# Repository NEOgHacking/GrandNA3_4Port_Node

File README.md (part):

# GrandNA3_4Port_Node
GrandNA3_4Port_Node is a DMX network node based on the official grandMA3 onPC 4Port Node 4k. My version also has 4DMX outputs with RDM support, a EtherCON connector for sturdy Ethernet connections and a display with a rotating knob for configuration. It also uses the Neutrik halo connectors with adressable rgb leds to show the status of the connection. But it also has some differences. First it unfortunately doesn't unlock any parameters in the GrandMA onPC software, but its 20x cheaper. About $100 instead of $2000.

# Features
This specific DMX node has some really usefull features.
1. 4DMX outputs with RDM support.
2. Neutrik EtherCON connector for a sturdy and lasting connection. Also support for ARTNET and sACN
3. Color display with a rotary encoder for configuration straigt from the unit itself.
4. UPS (uniteruptable power supply) For when the power cuts out but you still need it or just for battery operation.
5. Wifi card slot for wireless operation with the battery.
6. Powered by a rp2350 for its PIO modules so DMX is correctly implemented and not via a hacked uart or bitbanging a pin.
7. PoE (Power over Ethernet) For easy setup and as little wires as possible.
8. USB-C port for power and data to program the rp2350 or configure it.
9. Cheap PCB. The PCB is 100x72mm 4 layer so its cost is low only $7.

# Motivation
I started on making this DMX network node for a few reasons. First i was using a raspberry pi with a usb DMX dongle, this worked but was hard to set up and only got me 1 DMX universe without RDM. It also wasn't the cheapest setup. I wanted it to be cheaper and have more functionallity. Second I once had the opurtunity to use a grandMA3 onPC 4Port Node 4k at school once and realized how usefull it would be. Then my dumb brain said the same sentence it always says: "I can build that myself for cheaper right?" Next thing you know you are 100 hours deep into the project.

# Design
The design process was a heck of a ride, at first i started with the simple DMX part but then got to the ethernet. I really wanted PoE so started with the ride. It was a heck of a long ride, i think it took up 1/3 of the projects time its really complex. Also the most complex schematic from the whole project. The rest went pretty smooth. I had recently done another big project my 3D Printer mainboard and learned allot from that! So the rest was pretty straight forward, always some small chip changes here and there but apart from that it went well. The case design also went quick didn't have to high of standards for that but still wanted it to look good. After a whole day that was done. 
I used KiCad for PCB design, Onshape for 3D design and VScode for Firmware.

# Use
To use this product first get the firmware uploaded via the arduino IDE or PlatformIO Then just plug it into a ethernet setup and plug in your DMX devices. Thats it! Its that simple! For config use the display with the rotating knob to select universes, ethernet settings, ext.

# Schematic
This is a very long schematic. You can find the whole schematics in .PDF format in the individual PCB design folders. But here are some important ones.
First the main schematic of the main PCB.

Then the schematic of the display module.

And finally the esp wifi module.

# PCB's
So this project has 3 PCB's, first the main PCB that does all the hard work, then a display PCB with a rotary encoder and support components for a bare LCD and finally a custom made WIFI module PCB based on the esp.

(there is a glitch in this game, every project i do i get exactly 3 PCB's)

# Case
For this project there needed to be a case to protect the PCB from the outside world. I did this in onshape and am happy with the end result.

Here is the Onshape link:
https://cad.onshape.com/documents/7a1aa90c6a7c74ef8699231e/w/3ea57ea1703701009a206be9/e/21fe65d6bda3912845cd8de3?renderMode=0&uiState=69a73631645b04a633250657
<details>
  <summary>BOM</summary>
  
# BOM
| Id | Designator | Footprint | Quantity | Designation | Supplier and ref | Column1 | Needed quantity | - | LCSC | MOUSER | Already in another pcb | Enough? | Mrf# | Mfr. | Order Qty. | Unit Price(USD) | Ext.Price(USD) | LCSC#/MOUSER | Package | Min | Mult | SPQ | Availability | Stock Status | Customer Notes | Description | Matched status | Product Link |  |  |  |  |  |  |  |  |  |  |  |  |  |  |  |  |  |  |  |
| --- | --- | --- | --- | --- | --- | --- | --- | --- | --- | --- | --- | --- | --- | --- | --- | --- | --- | --- | --- | --- | --- | --- | --- | --- | --- | --- | --- | --- | --- | --- | --- | --- | --- | --- | --- | --- | --- | --- | --- | --- | --- | --- | --- | --- | --- | --- | --- |
| 17 | BT1 | JST_XH_B3B-XH-A_1x03_P2.50mm_Vertical | 1 | Battery_Cell |  |  | 2 |  | x |  |  |  | B3B-XH-A(LF)(SN) | JST | 10 | $0.05 | $0.50 | C144394 | Through Hole,P=2.5mm | 10 | 10 | 1000 | 61980 | In Stock |  | Connector Header 3 position 2.5mm Pitch 3A Through Hole -25?~+85? | Exact Matches | https://www.lcsc.com/product-detail/C144394.html |  |  |  |  |  |  |  |  |  |  |  |  |  |  |  |  |  |  |  |
| 6 | C12,C7,C5,C13,C11,C4,C6,C3,C9,C10,C8,C1 | C_0402_1005Metric | 12 | 100n |  |  | 24 |  | x |  |  |  | CL05B104KO5NNNC | Samsung Electro-Mechanics | 100 | $0.00 | $0.13 | C1525 | 402 | 100 | 100 | 10000 | 22016000 | In Stock |  | 100nF �10% 16V Ceramic Capacitor X7R 0402 | Exact Matches | https://www.lcsc.com/product-detail/C1525.html |  |  |  |  |  |  |  |  |  |  |  |  |  |  |  |  |  |  |  |
| 37 | C17,C19 | C_0402_1005Metric | 2 | 15p |  |  | 4 |  | x |  |  |  | CL05C150JB5NNNC | Samsung Electro-Mechanics | 100 | $0.00 | $0.37 | C86285 | 402 | 100 | 100 | 10000 | 454800 | In Stock |  | 15pF �5% 50V Ceramic Capacitor C0G 0402 | Exact Matches | https://www.lcsc.com/product-detail/C86285.html |  |  |  |  |  |  |  |  |  |  |  |  |  |  |  |  |  |  |  |
| 3 | C2,C15,C16,C14 | C_0402_1005Metric | 4 | 4u7 |  |  | 8 |  | x |  |  |  | CL05A475KP5NRNC | Samsung Electro-Mechanics | 50 | $0.01 | $0.31 | C368809 | 402 | 50 | 50 | 10000 | 5001000 | In Stock |  | 4.7uF �10% 10V Ceramic Capacitor X5R 0402 | Exact Matches | https://www.lcsc.com/product-detail/C368809.html |  |  |  |  |  |  |  |  |  |  |  |  |  |  |  |  |  |  |  |
| 9 | C20,C23,C57,C33,C21 | C_0603_1608Metric | 5 | 10n |  |  | 10 |  | x |  |  |  | CL10B103KC8NNNC | Samsung Electro-Mechanics | 100 | $0.01 | $0.62 | C84709 | 603 | 100 | 100 | 4000 | 18800 | In Stock |  | 10nF �10% 100V Ceramic Capacitor X7R 0603 | Exact Matches | https://www.lcsc.com/product-detail/C84709.html |  |  |  |  |  |  |  |  |  |  |  |  |  |  |  |  |  |  |  |
| 15 | C22,C36,C39,C41,C34,C38,C63,C37,C65,C47,C40,C35 | C_0603_1608Metric | 12 | 1n |  |  | 24 |  | x |  |  |  | CL10B102KC8NNNC | Samsung Electro-Mechanics | 50 | $0.01 | $0.25 | C153291 | 603 | 50 | 50 | 4000 | 107650 | In Stock |  | 1nF �10% 100V Ceramic Capacitor X7R 0603 | Exact Matches | https://www.lcsc.com/product-detail/C153291.html |  |  |  |  |  |  |  |  |  |  |  |  |  |  |  |  |  |  |  |
| 5 | C27,C76,C72,C70,C73,C64,C79,C60,C28,C74,C29,C88,C43,C78,C61,C71,C30,C66,C69,C68,C25,C42,C75,C67,C45,C31,C18,C26,C77 | C_0603_1608Metric | 29 | 100n |  |  | 58 |  | x |  |  |  | CL10B104KC8NNNC | Samsung Electro-Mechanics | 100 | $0.01 | $0.65 | C15725 | 603 | 50 | 50 | 4000 | 175750 | In Stock |  | 100nF �10% 100V Ceramic Capacitor X7R 0603 | Exact Matches | https://www.lcsc.com/product-detail/C15725.html |  |  |  |  |  |  |  |  |  |  |  |  |  |  |  |  |  |  |  |
| 63 | C32,C24 | CP_EIA-2012-12_Kemet-R | 2 | 10u |  |  | 4 |  | x |  |  |  | T491A106K006AT | KEMET | 5 | $0.18 | $0.91 | C122260 | CASE-A-3216-18(mm) | 5 | 5 | 2000 | 1980 | In Stock |  | 10uF �10% 6.3V Tantalum Capacitors 4?@100kHz CASE-A-3216-18(mm) | Exact Matches | https://www.lcsc.com/product-detail/C122260.html |  |  |  |  |  |  |  |  |  |  |  |  |  |  |  |  |  |  |  |
| 50 | C46,C44 | C_0603_1608Metric | 2 | 6.8n |  |  | 4 |  | x |  |  |  | CL10B682KB8NNNC | Samsung Electro-Mechanics | 100 | $0.01 | $0.68 | C84723 | 603 | 100 | 100 | 4000 | 5300 | In Stock |  | 6.8nF �10% 50V Ceramic Capacitor X7R 0603 | Exact Matches | https://www.lcsc.com/product-detail/C84723.html |  |  |  |  |  |  |  |  |  |  |  |  |  |  |  |  |  |  |  |
| 8 | C48,C49 | C_0603_1608Metric | 2 | 10p |  |  | 4 |  | x |  |  |  | CL10C100JB8NNNC | Samsung Electro-Mechanics | 100 | $0.01 | $0.50 | C1634 | 603 | 100 | 100 | 4000 | 1498600 | In Stock |  | 10pF �5% 50V Ceramic Capacitor C0G 0603 | Exact Matches | https://www.lcsc.com/product-detail/C1634.html |  |  |  |  |  |  |  |  |  |  |  |  |  |  |  |  |  |  |  |
| 41 | C52,C51,C50 | C_0805_2012Metric | 3 | 1u |  |  | 6 |  | x |  |  |  | C2012X7S2A105KT000N | TDK | 10 | $0.11 | $1.12 | C342785 | 805 | 5 | 5 | 2000 | 5645 | In Stock |  | 1uF �10% 100V Ceramic Capacitor X7S 0805 | Exact Matches | https://www.lcsc.com/product-detail/C342785.html |  |  |  |  |  |  |  |  |  |  |  |  |  |  |  |  |  |  |  |
| 57 | C53 | CP_Elec_6.3x5.8 | 1 | 10u |  |  | 2 |  | x |  |  |  | EEEFK1J100P | PANASONIC | 5 | $0.14 | $0.71 | C128459 | SMD,D6.3xL5.8mm | 5 | 5 | 1000 | 1420 | In Stock |  | 10uF �20% 63V Aluminum Electrolytic Capacitors 2000hrs@105? | Exact Matches | https://www.lcsc.com/product-detail/C128459.html |  |  |  |  |  |  |  |  |  |  |  |  |  |  |  |  |  |  |  |
| 69 | C54 | C_0603_1608Metric | 1 | 470p |  |  | 2 |  | x |  |  |  | CL10B471KB8NNNC | Samsung Electro-Mechanics | 100 | $0.01 | $0.56 | C22396 | 603 | 100 | 100 | 4000 | 189700 | In Stock |  | 470pF �10% 50V Ceramic Capacitor X7R 0603 | Exact Matches | https://www.lcsc.com/product-detail/C22396.html |  |  |  |  |  |  |  |  |  |  |  |  |  |  |  |  |  |  |  |
| 44 | C55 | CP_Elec_10x10.5 | 1 | 1000u |  |  | 2 |  | x |  |  |  | EEEFT1E102UP | PANASONIC | 2 | $0.78 | $1.55 | C401766 | SMD,D10xL10.2mm | 1 | 1 | 500 | 4041 | In Stock |  | 1000uF �20% 25V Aluminum Electrolytic Capacitors 2000hrs@105? | Exact Matches | https://www.lcsc.com/product-detail/C401766.html |  |  |  |  |  |  |  |  |  |  |  |  |  |  |  |  |  |  |  |
| 52 | C56 | C_1206_3216Metric | 1 | 100u |  |  | 2 |  | x |  |  |  | CL31A107MQHNNNE | Samsung Electro-Mechanics | 10 | $0.06 | $0.61 | C15008 | 1206 | 10 | 10 | 2000 | 6009890 | In Stock |  | 100uF �20% 6.3V Ceramic Capacitor X5R 1206 | Exact Matches | https://www.lcsc.com/product-detail/C15008.html |  |  |  |  |  |  |  |  |  |  |  |  |  |  |  |  |  |  |  |
| 14 | C58 | C_0603_1608Metric | 1 | 4u7 |  |  | 2 |  | x |  |  |  | CL10A475KP8NNNC | Samsung Electro-Mechanics | 50 | $0.01 | $0.28 | C1705 | 603 | 50 | 50 | 4000 | 13333100 | In Stock |  | 4.7uF �10% 10V Ceramic Capacitor X5R 0603 | Exact Matches | https://www.lcsc.com/product-detail/C1705.html |  |  |  |  |  |  |  |  |  |  |  |  |  |  |  |  |  |  |  |
| 20 | C59 | C_0603_1608Metric | 1 | 3.3n |  |  | 2 |  | x |  |  |  | CL10B332KB8NNNC | Samsung Electro-Mechanics | 20 | $0.01 | $0.11 | C1613 | 603 | 20 | 20 | 4000 | 61420 | In Stock |  | 3.3nF �10% 50V Ceramic Capacitor X7R 0603 | Exact Matches | https://www.lcsc.com/product-detail/C1613.html |  |  |  |  |  |  |  |  |  |  |  |  |  |  |  |  |  |  |  |
| 42 | C62 | C_0603_1608Metric | 1 | 15n |  |  | 2 |  | x |  |  |  | CL10B153KB8NNNC | Samsung Electro-Mechanics | 20 | $0.01 | $0.16 | C296713 | 603 | 20 | 20 | 4000 | 39800 | In Stock |  | 15nF �10% 50V Ceramic Capacitor X7R 0603 | Exact Matches | https://www.lcsc.com/product-detail/C296713.html |  |  |  |  |  |  |  |  |  |  |  |  |  |  |  |  |  |  |  |
| 10 | C80,C81 | C_0603_1608Metric | 2 | 1u |  |  | 4 |  | x |  |  |  | CL10A105KB8NNNC | Samsung Electro-Mechanics | 50 | $0.01 | $0.28 | C15849 | 603 | 50 | 50 | 4000 | 4548950 | In Stock |  | 1uF �10% 50V Ceramic Capacitor X5R 0603 | Exact Matches | https://www.lcsc.com/product-detail/C15849.html |  |  |  |  |  |  |  |  |  |  |  |  |  |  |  |  |  |  |  |
| 53 | C82,C86,C87,C83,C84 | C_0603_1608Metric | 5 | 10u |  |  | 10 |  | x |  |  |  | CL10A106KP8NNNC | Samsung Electro-Mechanics | 50 | $0.01 | $0.33 | C19702 | 603 | 50 | 50 | 4000 | 13475400 | In Stock |  | 10uF �10% 10V Ceramic Capacitor X5R 0603 | Exact Matches | https://www.lcsc.com/product-detail/C19702.html |  |  |  |  |  |  |  |  |  |  |  |  |  |  |  |  |  |  |  |
| 58 | C85 | C_0603_1608Metric | 1 | 2u2 |  |  | 2 |  | x |  |  |  | CL10A225KO8NNNC | Samsung Electro-Mechanics | 50 | $0.01 | $0.31 | C23630 | 603 | 50 | 50 | 4000 | 5941500 | In Stock |  | 2.2uF �10% 16V Ceramic Capacitor X5R 0603 | Exact Matches | https://www.lcsc.com/product-detail/C23630.html |  |  |  |  |  |  |  |  |  |  |  |  |  |  |  |  |  |  |  |
| 32 | D1 | D_SOD-123F | 1 | DSK24L |  |  | 2 |  | x |  |  |  | DSK24L | LGE | 10 | $0.06 | $0.62 | C19272974 | SOD-123FL | 10 | 10 | 3000 | 2600 | In Stock |  | Diode Independent 40V 2A Surface Mount SOD-123FL | Exact Matches | https://www.lcsc.com/product-detail/C19272974.html |  |  |  |  |  |  |  |  |  |  |  |  |  |  |  |  |  |  |  |
| 56 | D10 | D_SMA | 1 | SS34 |  |  | 2 |  | x |  |  |  | SS34 | GOODWORK | 20 | $0.03 | $0.56 | C908680 | SMA(DO-214AC) | 20 | 20 | 5000 | 202260 | In Stock |  | Diode Independent 40V 3A Surface Mount SMA(DO-214AC) | Exact Matches | https://www.lcsc.com/product-detail/C908680.html |  |  |  |  |  |  |  |  |  |  |  |  |  |  |  |  |  |  |  |
| 49 | D11 | D_SOD-123 | 1 | 1N4148W |  |  | 2 |  | x |  |  |  | 1N4148W-E3-08 | VISHAY | 5 | $0.03 | $0.17 | C241939 | SOD-123 | 5 | 5 | 3000 | 71145 | In Stock |  | Diode Independent 75V 150mA Surface Mount SOD-123 | Exact Matches | https://www.lcsc.com/product-detail/C241939.html |  |  |  |  |  |  |  |  |  |  |  |  |  |  |  |  |  |  |  |
| 66 | D12 | D_SOD-123F | 1 | DFTL30A |  |  | 2 |  | x |  |  |  | P4FL30A_R1_00001 | PANJIT | 5 | $0.09 | $0.43 | C2902532 | SOD-123FL | 5 | 5 | 3000 | 2220 | In Stock |  | 48.4VC Clamp 8.3A@10/1000us Ipp TVS DIODE SOD-123FL | Exact Matches | https://www.lcsc.com/product-detail/C2902532.html |  |  |  |  |  |  |  |  |  |  |  |  |  |  |  |  |  |  |  |
| 11 | D13 | LED-SMD_4P-L1.6-W1.5-TR | 1 | LED_ABGR |  |  | 2 |  | x |  |  |  | DY-S161506BRGC-T5-4T-03 | TONYU | 10 | $0.04 | $0.37 | C7280953 | SMD,1.6x1.5mm | 10 | 10 | 4000 | 1640 | In Stock |  | Red, Green, Blue 630nm LED Indication - Discrete 1.8V~2.4V SMD,1.5x1.6mm | Exact Matches | https://www.lcsc.com/product-detail/C7280953.html |  |  |  |  |  |  |  |  |  |  |  |  |  |  |  |  |  |  |  |
| 28 | D2,D7,D5,D6,D9,D3,D4,D8 | D_SOD-123F | 8 | SL110PL-TP |  |  | 16 |  | x |  |  |  | SL110PL-TP | MCC | 20 | $0.15 | $3.07 | C7080765 | SOD-123FL | 10 | 10 | 2500 | 4140 | In Stock |  | Diode 100V 1A Surface Mount SOD-123FL | Exact Matches | https://www.lcsc.com/product-detail/C7080765.html |  |  |  |  |  |  |  |  |  |  |  |  |  |  |  |  |  |  |  |
| 62 | IC1 | QFN-32-1EP_5x5mm_P0.5mm_EP3.45x3.45mm_ThermalVias | 1 | NPM1300-QEAA-R7 |  |  | 2 |  |  | x |  |  | nPM1300-QEAA-R7 | Nordic Semiconductor | 2 | $1.54 | $3.08 | 949-NPM1300-QEAA-R7 |  |  |  |  |  |  |  |  |  | https://nl.mouser.com/ProductDetail/Nordic-Semiconductor/nPM1300-QEAA-R7?qs=3pZoU%2F6IRTj0hxAp51B2zA%3D%3D |  |  |  |  |  |  |  |  |  |  |  |  |  |  |  |  |  |  |  |
| 33 | J1 | JST_SH_SM03B-SRSS-TB_1x03-1MP_P1.00mm_Horizontal | 1 | Conn_01x03_MountingPin |  |  | 2 |  | x |  |  |  | SM03B-SRSS-TB(LF)(SN) | JST | 5 | $0.17 | $0.87 | C160403 | SMD,P=1mm,Surface Mount,Right Angle | 5 | 5 | 3000 | 47315 | In Stock |  | Connector Header 3 position 1mm Pitch 1A Surface Mount, Right Angle -25?~+85? | Exact Matches | https://www.lcsc.com/product-detail/C160403.html |  |  |  |  |  |  |  |  |  |  |  |  |  |  |  |  |  |  |  |
| 39 | J12 | IDC-Header_2x06_P2.54mm_Vertical | 1 | IDC |  |  | 2 |  | x |  |  |  | 2.54-2*6P | BOOMELE(Boom Precision Elec) | 5 | $0.11 | $0.57 | C9136 | Through Hole,P=2.54mm | 5 | 5 | 220 | 19840 | In Stock |  | Connector IDC Header Through Hole 12 position 2.54mm | Exact Matches | https://www.lcsc.com/product-detail/C9136.html |  |  |  |  |  |  |  |  |  |  |  |  |  |  |  |  |  |  |  |
| 51 | J13 | PinSocket_2x04_P2.54mm_Vertical | 1 | Conn_02x04 |  |  | 2 |  | x |  |  |  | PM254V-12-08-H85 | XFCN | 5 | $0.11 | $0.56 | C2834799 | Through Hole,P=2.54mm | 5 | 5 | 1000 | 26375 | In Stock |  | Female Header 8 Position 2.54mm Pitch Dual Row Through Hole -40?~+105? | Exact Matches | https://www.lcsc.com/product-detail/C2834799.html |  |  |  |  |  |  |  |  |  |  |  |  |  |  |  |  |  |  |  |
| 13 | J2 | USB-C_SMD-TYPE-C-31-M-12_1 | 1 | USB_C_Receptacle_USB2.0_14P |  |  | 2 |  | x |  |  |  | TYPE-C-31-M-12 | Korean Hroparts Elec | 5 | $0.17 | $0.84 | C165948 | SMD | 5 | 5 | 1000 | 263130 | In Stock |  | USB-C (USB TYPE-C) Receptacle Connector 16 Position Surface Mount | Exact Matches | https://www.lcsc.com/product-detail/C165948.html |  |  |  |  |  |  |  |  |  |  |  |  |  |  |  |  |  |  |  |
| 1 | J3 | NE8FAHLRDAE | 1 | RJ45 |  |  | 2 |  |  | x |  |  | NE8FAH-LR-DAE | Neutrik | 2 | $6.73 | $13.46 | 568-NE8FAH-LR-DAE |  |  |  |  |  |  |  |  |  | https://nl.mouser.com/ProductDetail/Neutrik/NE8FAH-LR-DAE?qs=4ASt3YYao0WhX9cY4j%252BFSA%3D%3D |  |  |  |  |  |  |  |  |  |  |  |  |  |  |  |  |  |  |  |
| 12 | J4,J8,J10,J6 | NC5FAH1-LR-DAE | 4 | XLR5 |  |  | 4 |  |  | x |  |  | NC5FAH1-LR-DAE | Neutrik | 4 | $7.79 | $31.16 | 568-NC5FAH1-LR-DAE |  |  |  |  |  |  |  |  |  | https://nl.mouser.com/ProductDetail/Neutrik/NC5FAH1-LR-DAE?qs=6avfeC6zeS5u3oz5Q9UQlw%3D%3D |  |  |  |  |  |  |  |  |  |  |  |  |  |  |  |  |  |  |  |
| 47 | J7,J11,J5,J9 | NC3FAH2-LR-DAE | 4 | XLR3 |  |  | 4 |  |  | x |  |  | NC3FAH2-LR-DAE | Neutrik | 4 | $4.33 | $17.32 | 568-NC3FAH2-LR-DAE |  |  |  |  |  |  |  |  |  | https://nl.mouser.com/ProductDetail/Neutrik/NC3FAH2-LR-DAE?qs=4ASt3YYao0XSl5KoEkZrIA%3D%3D |  |  |  |  |  |  |  |  |  |  |  |  |  |  |  |  |  |  |  |
| 21 | L1 | IND-SMD_L2.0-W1.6_AOTA-B201610S3R3-101-T | 1 | 3.3u |  |  | 2 |  | x |  |  |  | AOTA-B201610S3R3-101-T | ABRACON | 5 | $0.29 | $1.44 | C42411119 | 806 | 5 | 5 | 3000 | 15360 | In Stock |  | 2.1A 3.3uH 115m? 2.4A Molded Inductor 0806 Fixed Inductors RoHS | Exact Matches | https://www.lcsc.com/product-detail/C42411119.html |  |  |  |  |  |  |  |  |  |  |  |  |  |  |  |  |  |  |  |
| 48 | L2 | L_Vishay_IHLP-1616 | 1 | 1u |  |  | 2 |  | x |  |  |  | IHLP1616BZER1R0M11 | VISHAY | 2 | $1.63 | $3.26 | C844978 | 1616 | 1 | 1 | 4000 | 79 | In Stock |  | 4.5A 1uH 27m? 5A �20% 1616 Fixed Inductors RoHS | Exact Matches | https://www.lcsc.com/product-detail/C844978.html |  |  |  |  |  |  |  |  |  |  |  |  |  |  |  |  |  |  |  |
| 22 | L3 | XFMR-SMD_16P-L12.7-W7.1-P1.27-LS9.4-BL | 1 | H2019NLT |  |  | 2 |  | x |  |  |  | H2019NLT | PULSE | 2 | $0.74 | $1.49 | C110250 | SMD,12.7x7.1mm | 1 | 1 | 600 | 2085 | In Stock |  | LAN Transformer 1CT:1CT Surface Mount,12.7x7.1mm | Exact Matches | https://www.lcsc.com/product-detail/C110250.html |  |  |  |  |  |  |  |  |  |  |  |  |  |  |  |  |  |  |  |
| 30 | L4,L5 | L_0805_2012Metric | 2 | 2u2 |  |  | 4 |  | x |  |  |  | MLP2012H2R2MT0S1 | TDK | 10 | $0.08 | $0.84 | C383369 | 805 | 10 | 10 | 4000 | 89820 | In Stock |  | 1A 2.2uH 195m? �20% 0805 Fixed Inductors RoHS | Exact Matches | https://www.lcsc.com/product-detail/C383369.html |  |  |  |  |  |  |  |  |  |  |  |  |  |  |  |  |  |  |  |
| 16 | LED1,LED5,LED6,LED3,LED8,LED10,LED9,LED2,LED4,LED7 | LED-SMD_4P-L1.5-W1.5-BL | 10 | SK6805-EC15 |  |  | 20 |  | x |  |  |  | SK6805-EC15 | OPSCO Optoelectronics | 45 | $0.09 | $4.04 | C2890035 | SMD-4P,1.5x1.5mm | 5 | 5 | 4500 | 259070 | In Stock |  | SMD-4P,1.5x1.5mm LED Addressable, Specialty RoHS | Exact Matches | https://www.lcsc.com/product-detail/C2890035.html |  |  |  |  |  |  |  |  |  |  |  |  |  |  |  |  |  |  |  |
| 29 | R1,R27,R3 | R_0603_1608Metric | 3 | 1k |  |  | 6 |  | x |  |  |  | RC0603FR-071KL | YAGEO | 100 | $0.00 | $0.14 | C22548 | 603 | 100 | 100 | 5000 | 4596000 | In Stock |  | 100mW 1k? 75V Thick Film Resistor �100ppm/? �1% 0603 Chip Resistor - Surface Mount RoHS | Exact Matches | https://www.lcsc.com/product-detail/C22548.html |  |  |  |  |  |  |  |  |  |  |  |  |  |  |  |  |  |  |  |
| 34 | R11,R43,R7,R42 | R_0603_1608Metric | 4 | 10k |  |  | 8 |  | x |  |  |  | RC0603FR-0710KL | YAGEO | 100 | $0.00 | $0.14 | C98220 | 603 | 100 | 100 | 5000 | 9034300 | In Stock |  | 100mW 10k? 75V Thick Film Resistor �100ppm/? �1% 0603 Chip Resistor - Surface Mount RoHS | Exact Matches | https://www.lcsc.com/product-detail/C98220.html |  |  |  |  |  |  |  |  |  |  |  |  |  |  |  |  |  |  |  |
| 19 | R13,R12,R15,R14 | R_0603_1608Metric | 4 | 33R |  |  | 8 |  | x |  |  |  | RC0603FR-0733RL | YAGEO | 100 | $0.00 | $0.15 | C108661 | 603 | 100 | 100 | 5000 | 1912100 | In Stock |  | 100mW 33? 75V Thick Film Resistor �100ppm/? �1% 0603 Chip Resistor - Surface Mount RoHS | Exact Matches | https://www.lcsc.com/product-detail/C108661.html |  |  |  |  |  |  |  |  |  |  |  |  |  |  |  |  |  |  |  |
| 38 | R16 | R_0603_1608Metric | 1 | 1M |  |  | 2 |  | x |  |  |  | RC0603FR-071ML | YAGEO | 100 | $0.00 | $0.15 | C105578 | 603 | 100 | 100 | 5000 | 711300 | In Stock |  | 100mW 1M? 75V Thick Film Resistor �100ppm/? �1% 0603 Chip Resistor - Surface Mount RoHS | Exact Matches | https://www.lcsc.com/product-detail/C105578.html |  |  |  |  |  |  |  |  |  |  |  |  |  |  |  |  |  |  |  |
| 2 | R18 | R_0603_1608Metric | 1 | 10R |  |  | 2 |  | x |  |  |  | RC0603FR-0710RL | YAGEO | 100 | $0.00 | $0.43 | C109318 | 603 | 100 | 100 | 5000 | 1937200 | In Stock |  | 100mW 10? 75V Thick Film Resistor �1% �200ppm/? 0603 Chip Resistor - Surface Mount RoHS | Exact Matches | https://www.lcsc.com/product-detail/C109318.html |  |  |  |  |  |  |  |  |  |  |  |  |  |  |  |  |  |  |  |
| 72 | R19 | R_0603_1608Metric | 1 | 12.4k |  |  | 2 |  | x |  |  |  | RC0603FR-0712K4L | YAGEO | 100 | $0.00 | $0.15 | C137798 | 603 | 100 | 100 | 5000 | 38200 | In Stock |  | 100mW 12.4k? 75V Thick Film Resistor �100ppm/? �1% 0603 Chip Resistor - Surface Mount RoHS | Exact Matches | https://www.lcsc.com/product-detail/C137798.html |  |  |  |  |  |  |  |  |  |  |  |  |  |  |  |  |  |  |  |
| 54 | R2 | R_0402_1005Metric | 1 | 33R |  |  | 2 |  | x |  |  |  | RC0402FR-0733RL | YAGEO | 100 | $0.00 | $0.08 | C138002 | 402 | 100 | 100 | 10000 | 1384200 | In Stock |  | 62.5mW 33? 50V Thick Film Resistor �100ppm/? �1% 0402 Chip Resistor - Surface Mount RoHS | Exact Matches | https://www.lcsc.com/product-detail/C138002.html |  |  |  |  |  |  |  |  |  |  |  |  |  |  |  |  |  |  |  |
| 73 | R20 | R_0603_1608Metric | 1 | 4.99k |  |  | 2 |  | x |  |  |  | RC0603FR-074K99L | YAGEO | 100 | $0.00 | $0.15 | C114621 | 603 | 100 | 100 | 5000 | 164800 | In Stock |  | 100mW 4.99k? 75V Thick Film Resistor �100ppm/? �1% 0603 Chip Resistor - Surface Mount RoHS | Exact Matches | https://www.lcsc.com/product-detail/C114621.html |  |  |  |  |  |  |  |  |  |  |  |  |  |  |  |  |  |  |  |
| 24 | R21 | R_0603_1608Metric | 1 | 2.05k |  |  | 2 |  | x |  |  |  | RC0603FR-072K05L | YAGEO | 100 | $0.00 | $0.14 | C137751 | 603 | 100 | 100 | 5000 | 7700 | In Stock |  | 100mW 2.05k? 75V Thick Film Resistor �100ppm/? �1% 0603 Chip Resistor - Surface Mount RoHS | Exact Matches | https://www.lcsc.com/product-detail/C137751.html |  |  |  |  |  |  |  |  |  |  |  |  |  |  |  |  |  |  |  |
| 46 | R22,R40,R23,R17,R8 | R_0603_1608Metric | 5 | 0R |  |  | 10 |  | x |  |  |  | RC0603FR-070RL | YAGEO | 100 | $0.00 | $0.13 | C100044 | 603 | 100 | 100 | 5000 | 2174100 | In Stock |  | 0? 100mW 75V Thick Film Resistor �1% 0603 Chip Resistor - Surface Mount RoHS | Exact Matches | https://www.lcsc.com/product-detail/C100044.html |  |  |  |  |  |  |  |  |  |  |  |  |  |  |  |  |  |  |  |
| 55 | R24 | R_0603_1608Metric | 1 | 36.5k |  |  | 2 |  | x |  |  |  | RC0603FR-0736K5L | YAGEO | 100 | $0.00 | $0.14 | C137738 | 603 | 100 | 100 | 5000 | 20500 | In Stock |  | 36.5k? 100mW 75V Thick Film Resistor �100ppm/? �1% 0603 Chip Resistor - Surface Mount RoHS | Exact Matches | https://www.lcsc.com/product-detail/C137738.html |  |  |  |  |  |  |  |  |  |  |  |  |  |  |  |  |  |  |  |
| 68 | R25 | R_0603_1608Metric | 1 | 12.1k |  |  | 2 |  | x |  |  |  | RC0603FR-0712K1L | YAGEO | 100 | $0.00 | $0.18 | C123417 | 603 | 100 | 100 | 5000 | 0 | Backordered |  | 100mW 12.1k? 75V Thick Film Resistor �100ppm/? �1% 0603 Chip Resistor - Surface Mount RoHS | Exact Matches | https://www.lcsc.com/product-detail/C123417.html |  |  |  |  |  |  |  |  |  |  |  |  |  |  |  |  |  |  |  |
| 67 | R26 | R_0603_1608Metric | 1 | 24.9k |  |  | 2 |  | x |  |  |  | RC0603FR-0724K9L | YAGEO | 100 | $0.00 | $0.15 | C137761 | 603 | 100 | 100 | 5000 | 0 | Backordered |  | 100mW 24.9k? 75V Thick Film Resistor �100ppm/? �1% 0603 Chip Resistor - Surface Mount RoHS | Exact Matches | https://www.lcsc.com/product-detail/C137761.html |  |  |  |  |  |  |  |  |  |  |  |  |  |  |  |  |  |  |  |
| 4 | R29,R38,R28,R30,R39,R31,R36,R37 | R_0603_1608Metric | 8 | 348R |  |  | 16 |  | x |  |  |  | RC0603FR-07348RL | YAGEO | 100 | $0.00 | $0.14 | C137742 | 603 | 100 | 100 | 5000 | 6700 | In Stock |  | 100mW 348? 75V Thick Film Resistor �100ppm/? �1% 0603 Chip Resistor - Surface Mount RoHS | Exact Matches | https://www.lcsc.com/product-detail/C137742.html |  |  |  |  |  |  |  |  |  |  |  |  |  |  |  |  |  |  |  |
| 26 | R33,R32,R35,R34 | R_0603_1608Metric | 4 | 133R |  |  | 8 |  | x |  |  |  | RC0603FR-07133RL | YAGEO | 100 | $0.00 | $0.07 | C273752 | 603 | 100 | 100 | 5000 | 0 | Backordered |  | 133? 100mW 75V Thick Film Resistor �100ppm/? �1% 0603 Chip Resistor - Surface Mount RoHS | Exact Matches | https://www.lcsc.com/product-detail/C273752.html |  |  |  |  |  |  |  |  |  |  |  |  |  |  |  |  |  |  |  |
| 61 | R41 | R_0603_1608Metric | 1 | 430k |  |  | 2 |  | x |  |  |  | RC0603FR-07430KL | YAGEO | 100 | $0.00 | $0.15 | C482869 | 603 | 100 | 100 | 5000 | 30900 | In Stock |  | 430k? 100mW 75V Thick Film Resistor �100ppm/? �1% 0603 Chip Resistor - Surface Mount RoHS | Exact Matches | https://www.lcsc.com/product-detail/C482869.html |  |  |  |  |  |  |  |  |  |  |  |  |  |  |  |  |  |  |  |
| 7 | R5,R4 | R_0402_1005Metric | 2 | 27R |  |  | 4 |  | x |  |  |  | RC0402FR-0727RL | YAGEO | 100 | $0.00 | $0.09 | C138021 | 402 | 100 | 100 | 10000 | 134000 | In Stock |  | 27? �1% 62.5mW 0402 Thick Film Resistor | Exact Matches | https://www.lcsc.com/product-detail/C138021.html |  |  |  |  |  |  |  |  |  |  |  |  |  |  |  |  |  |  |  |
| 64 | R6 | R_0402_1005Metric | 1 | 1k |  |  | 2 |  | x |  |  |  | RC0402FR-071KL | YAGEO | 100 | $0.00 | $0.08 | C106235 | 402 | 100 | 100 | 10000 | 5619500 | In Stock |  | 1k? 62.5mW 50V Thick Film Resistor �100ppm/? �1% 0402 Chip Resistor - Surface Mount RoHS | Exact Matches | https://www.lcsc.com/product-detail/C106235.html |  |  |  |  |  |  |  |  |  |  |  |  |  |  |  |  |  |  |  |
| 45 | REF**,REF**,REF** | NLR-LB | 3 | NLR-LB |  |  | 6 |  |  | x |  |  | NLR-LB | Neutrik | 6 | $1.01 | $6.06 | 568-NLR-LB |  |  |  |  |  |  |  |  |  | https://nl.mouser.com/ProductDetail/Neutrik/NLR-LB?qs=Imq1NPwxi76abBKVKeKReg%3D%3D |  |  |  |  |  |  |  |  |  |  |  |  |  |  |  |  |  |  |  |
| 36 | RN1,RN2 | R_Array_Concave_4x0603 | 2 | 75R |  |  | 4 |  | x |  |  |  | RTA03-4D750JTP | RALEC | 100 | $0.01 | $0.50 | C102680 | 0603x4 | 100 | 100 | 5000 | 584400 | In Stock |  | 4 �5% 75? 62.5mW �200ppm/? 0603x4 Resistor Networks, Arrays RoHS | Exact Matches | https://www.lcsc.com/product-detail/C102680.html |  |  |  |  |  |  |  |  |  |  |  |  |  |  |  |  |  |  |  |
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
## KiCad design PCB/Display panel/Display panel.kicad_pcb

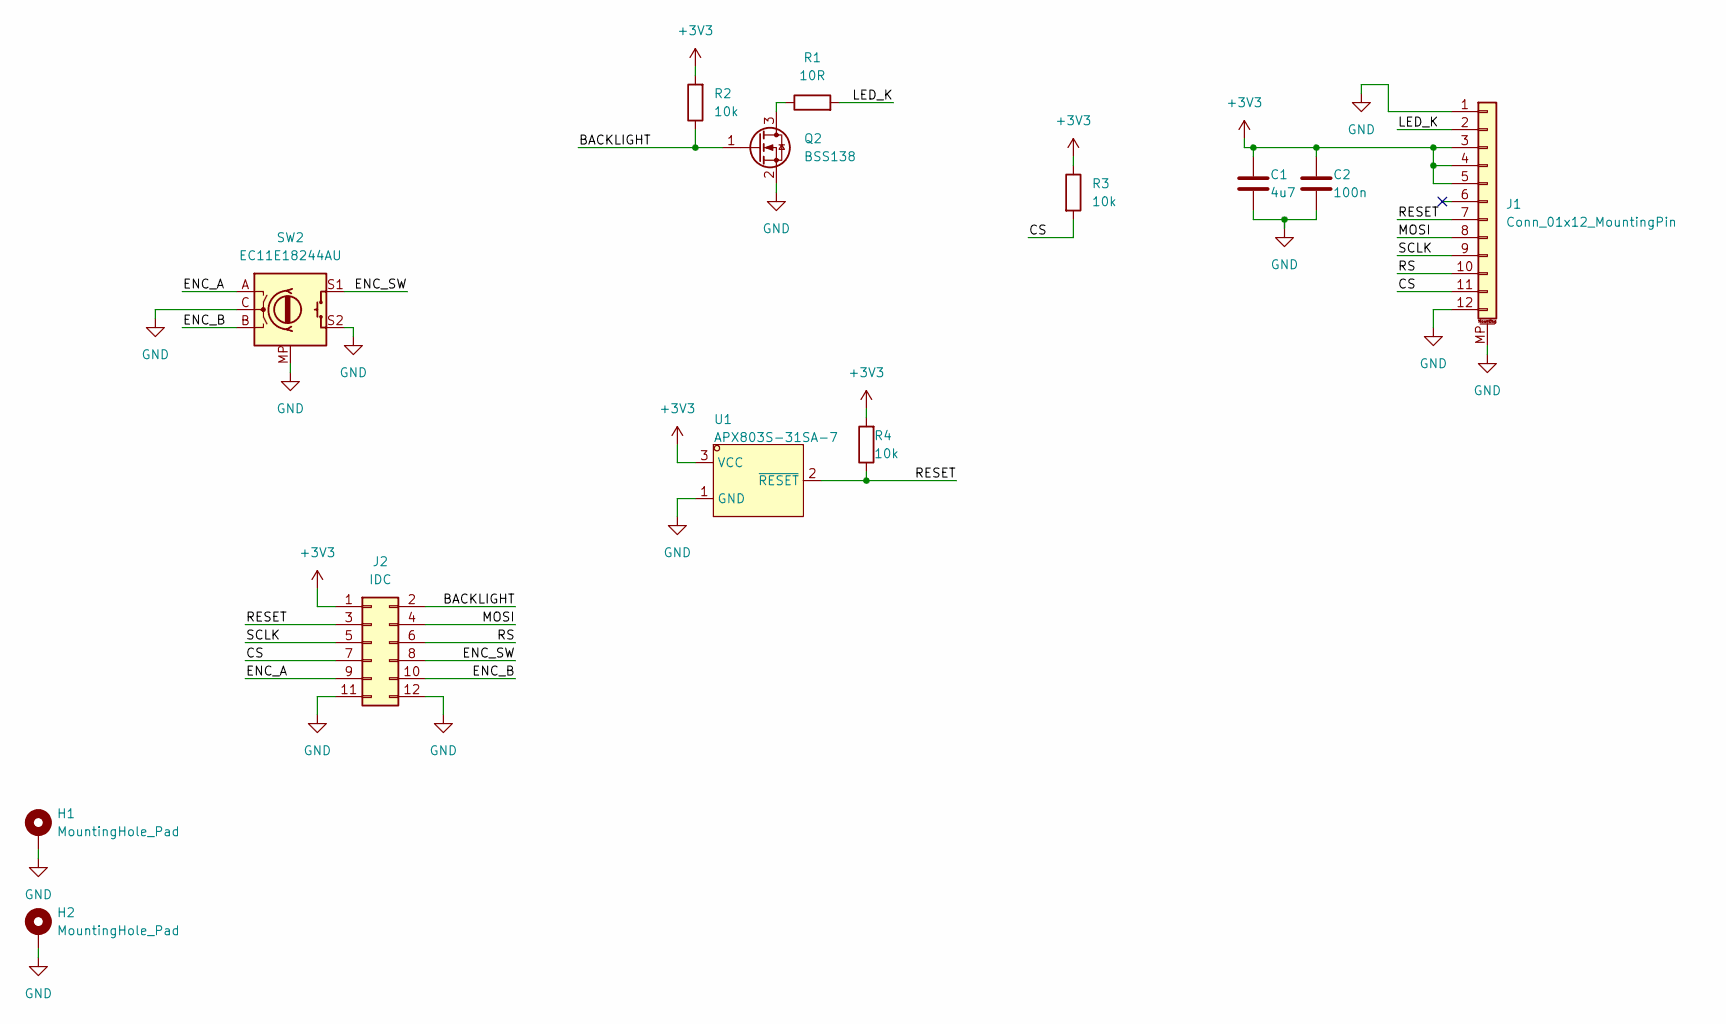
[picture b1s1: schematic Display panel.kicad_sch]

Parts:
C1: 4u7; C_0603_1608Metric
C2: 100n; C_0603_1608Metric
H1, H2: MountingHole_Pad; MountingHole_3.2mm_M3_Pad
J1: Conn_01x12_MountingPin; FPC-SMD_5034801200
J2: IDC; IDC-Header_2x06_P2.54mm_Vertical
Q2: BSS138; SOT-23
R1: 10R; R_0603_1608Metric
R2, R3, R4: 10k; R_0603_1608Metric
SW2: EC11E18244AU; RotaryEncoder_Alps_EC11E-Switch_Vertical_H20mm
U1: APX803S-31SA-7; SOT-23; LCSC Part C129757

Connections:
+3V3: C1.1, C2.1, J1.3, J1.4, J1.5, J2.1, R2.2, R3.1, R4.2, U1.3 (VCC)
/BACKLIGHT: J2.2, Q2.1 (G), R2.1
/CS: J1.11, J2.7, R3.2
/ENC_A: J2.9, SW2.A
/ENC_B: J2.10, SW2.B
/ENC_SW: J2.8, SW2.S1
/LED_K: J1.2, R1.2
/MOSI: J1.8, J2.4
/RESET: J1.7, J2.3, R4.1, U1.2 (~RESET)
/RS: J1.10, J2.6
/SCLK: J1.9, J2.5
GND: C1.2, C2.2, H1.1, H2.1, J1.1, J1.12, J1.MP (MountPin), J2.11, J2.12, Q2.2 (S), SW2.C, SW2.MP, SW2.S2, U1.1 (GND)
unnamed: Q2.3 (D), R1.1

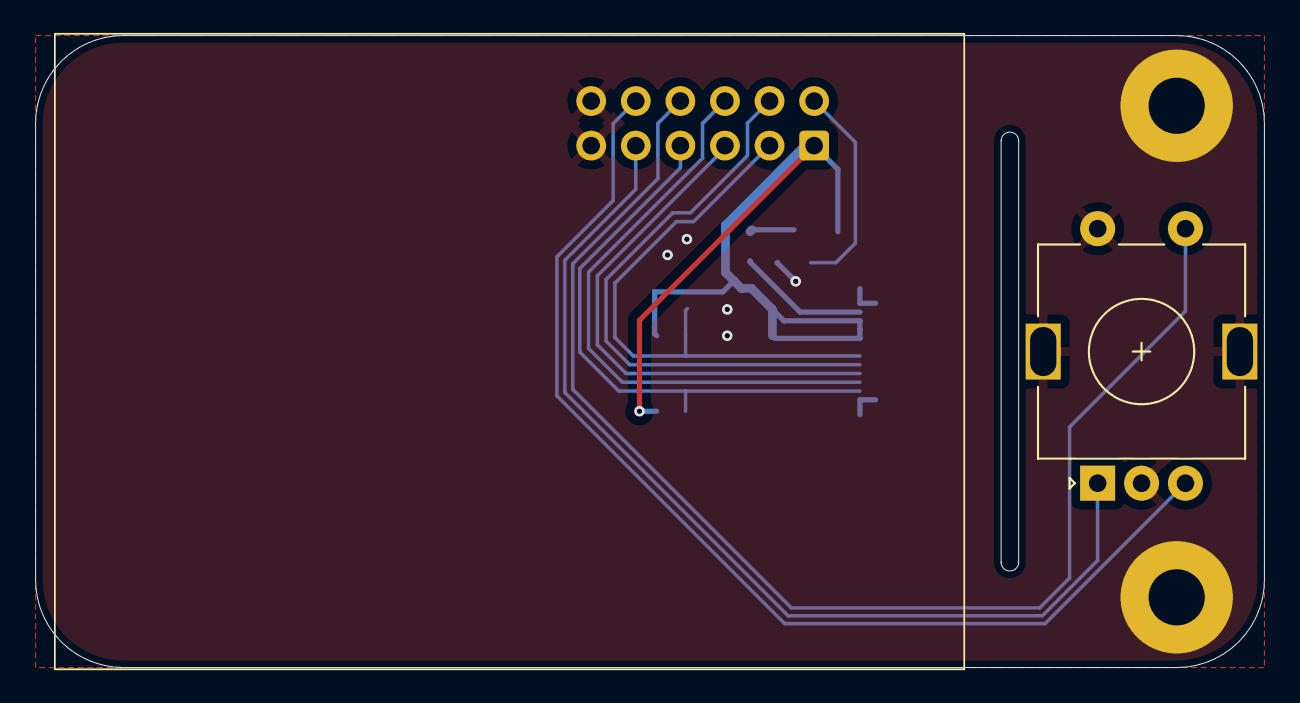
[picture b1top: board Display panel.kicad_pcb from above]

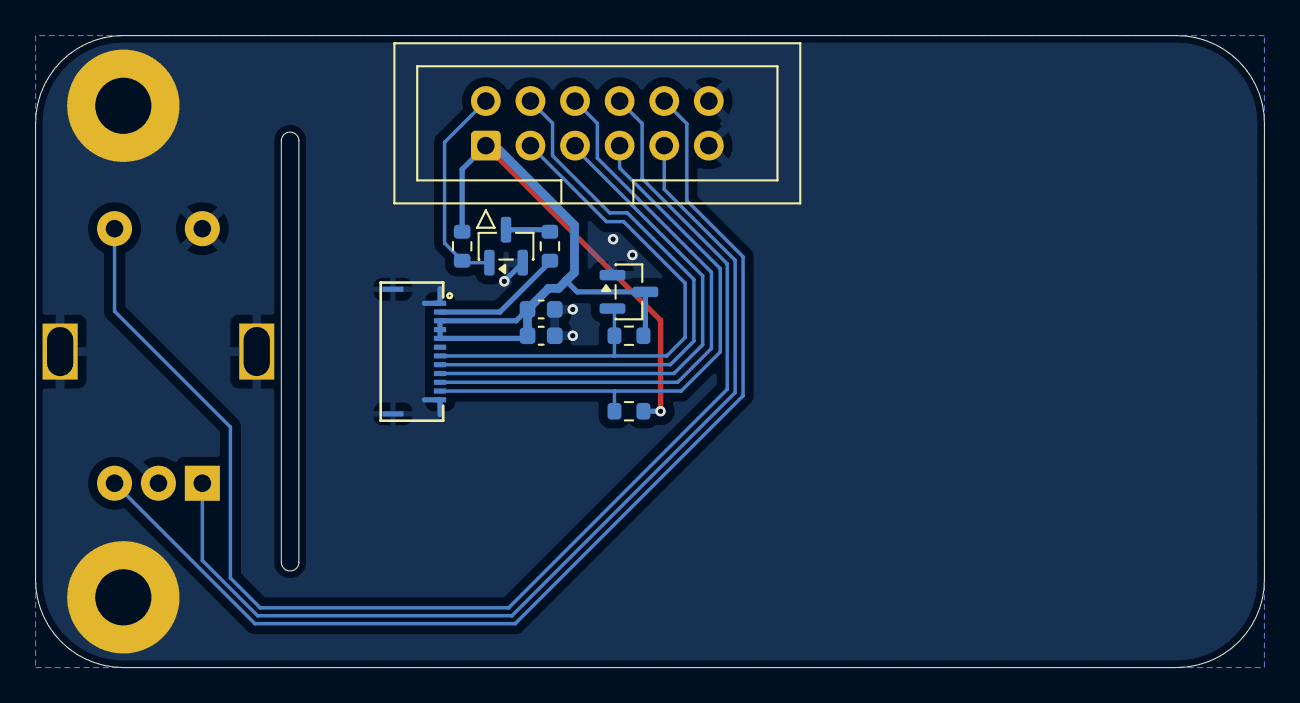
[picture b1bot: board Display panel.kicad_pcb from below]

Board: 2 copper layers, 70.0 x 36.0 mm, 13 parts (10 on the bottom side), 13 nets.

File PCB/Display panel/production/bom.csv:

Designator,Footprint,Quantity,Value,LCSC Part #
C1,0603,1,4u7,
C2,0603,1,100n,
J1,FPC-SMD_5034801200,1,Conn_01x12_MountingPin,
J2,IDC-Header_2x06_P2.54mm_Vertical,1,IDC,
Q2,SOT-23,1,BSS138,
R1,0603,1,10R,
"R2, R3, R4",0603,3,10k,
SW2,RotaryEncoder_Alps_EC11E-Switch_Vertical_H20mm,1,EC11E18244AU,
U1,SOT-23,1,APX803S-31SA-7,C129757

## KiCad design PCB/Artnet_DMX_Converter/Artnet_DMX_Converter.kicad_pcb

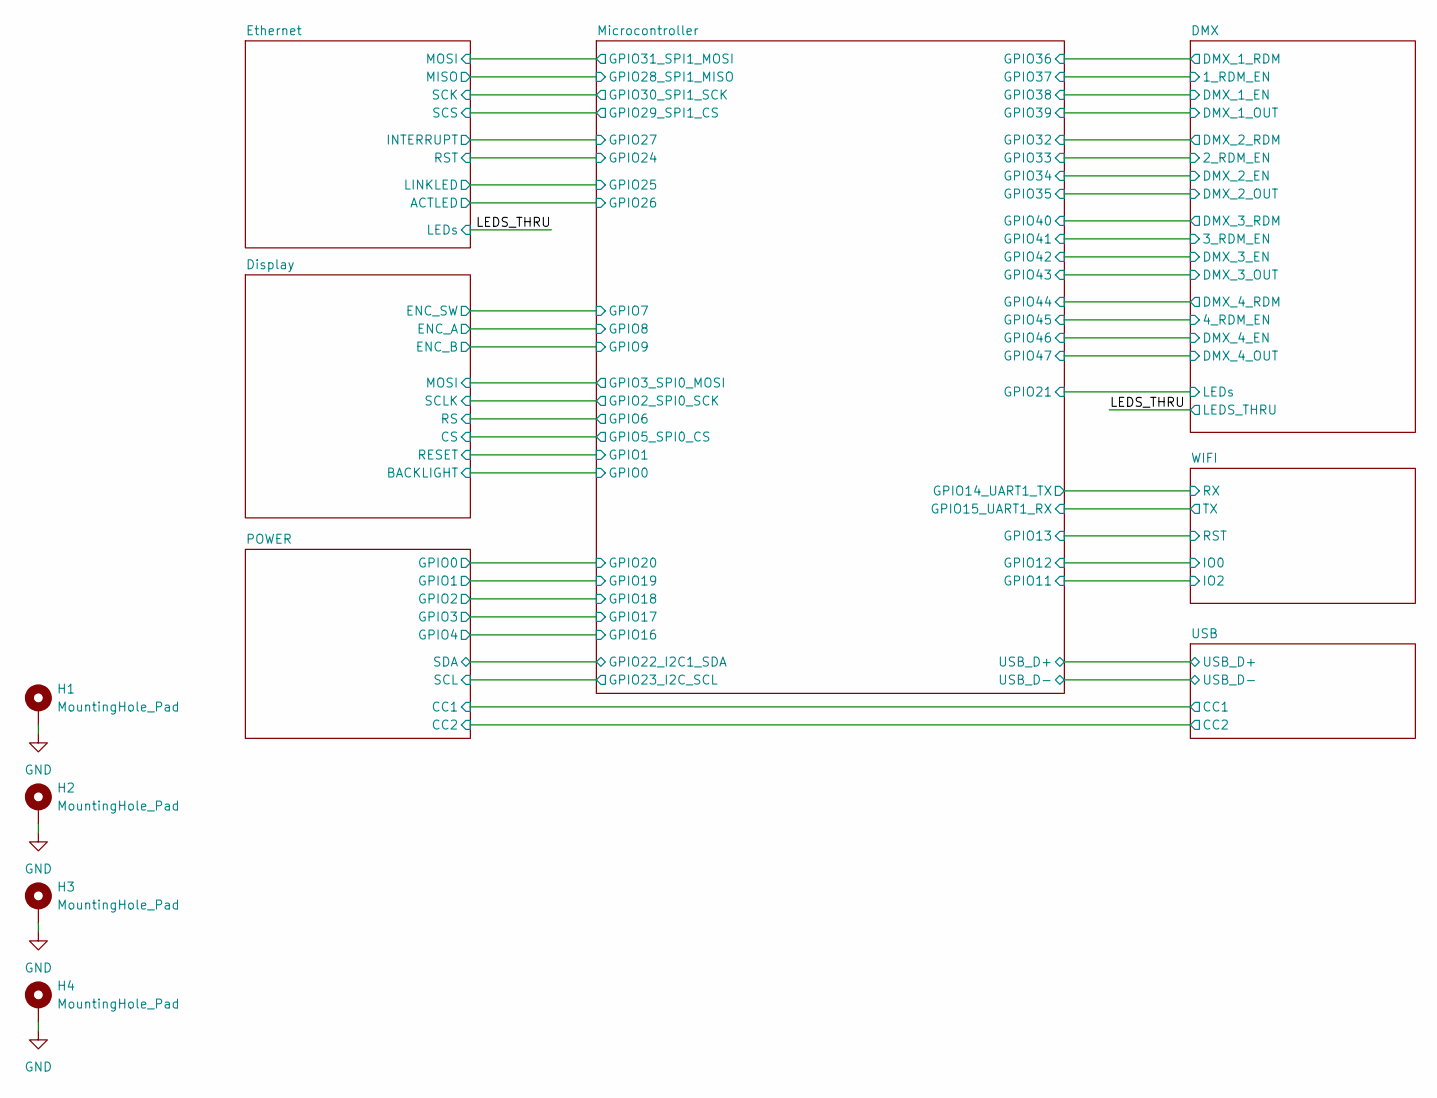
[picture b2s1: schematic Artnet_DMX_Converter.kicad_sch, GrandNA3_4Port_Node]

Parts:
H1, H2, H3, H4: MountingHole_Pad; MountingHole_3.2mm_M3_Pad

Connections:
GND: H1.1, H2.1, H3.1, H4.1; also elsewhere on the board

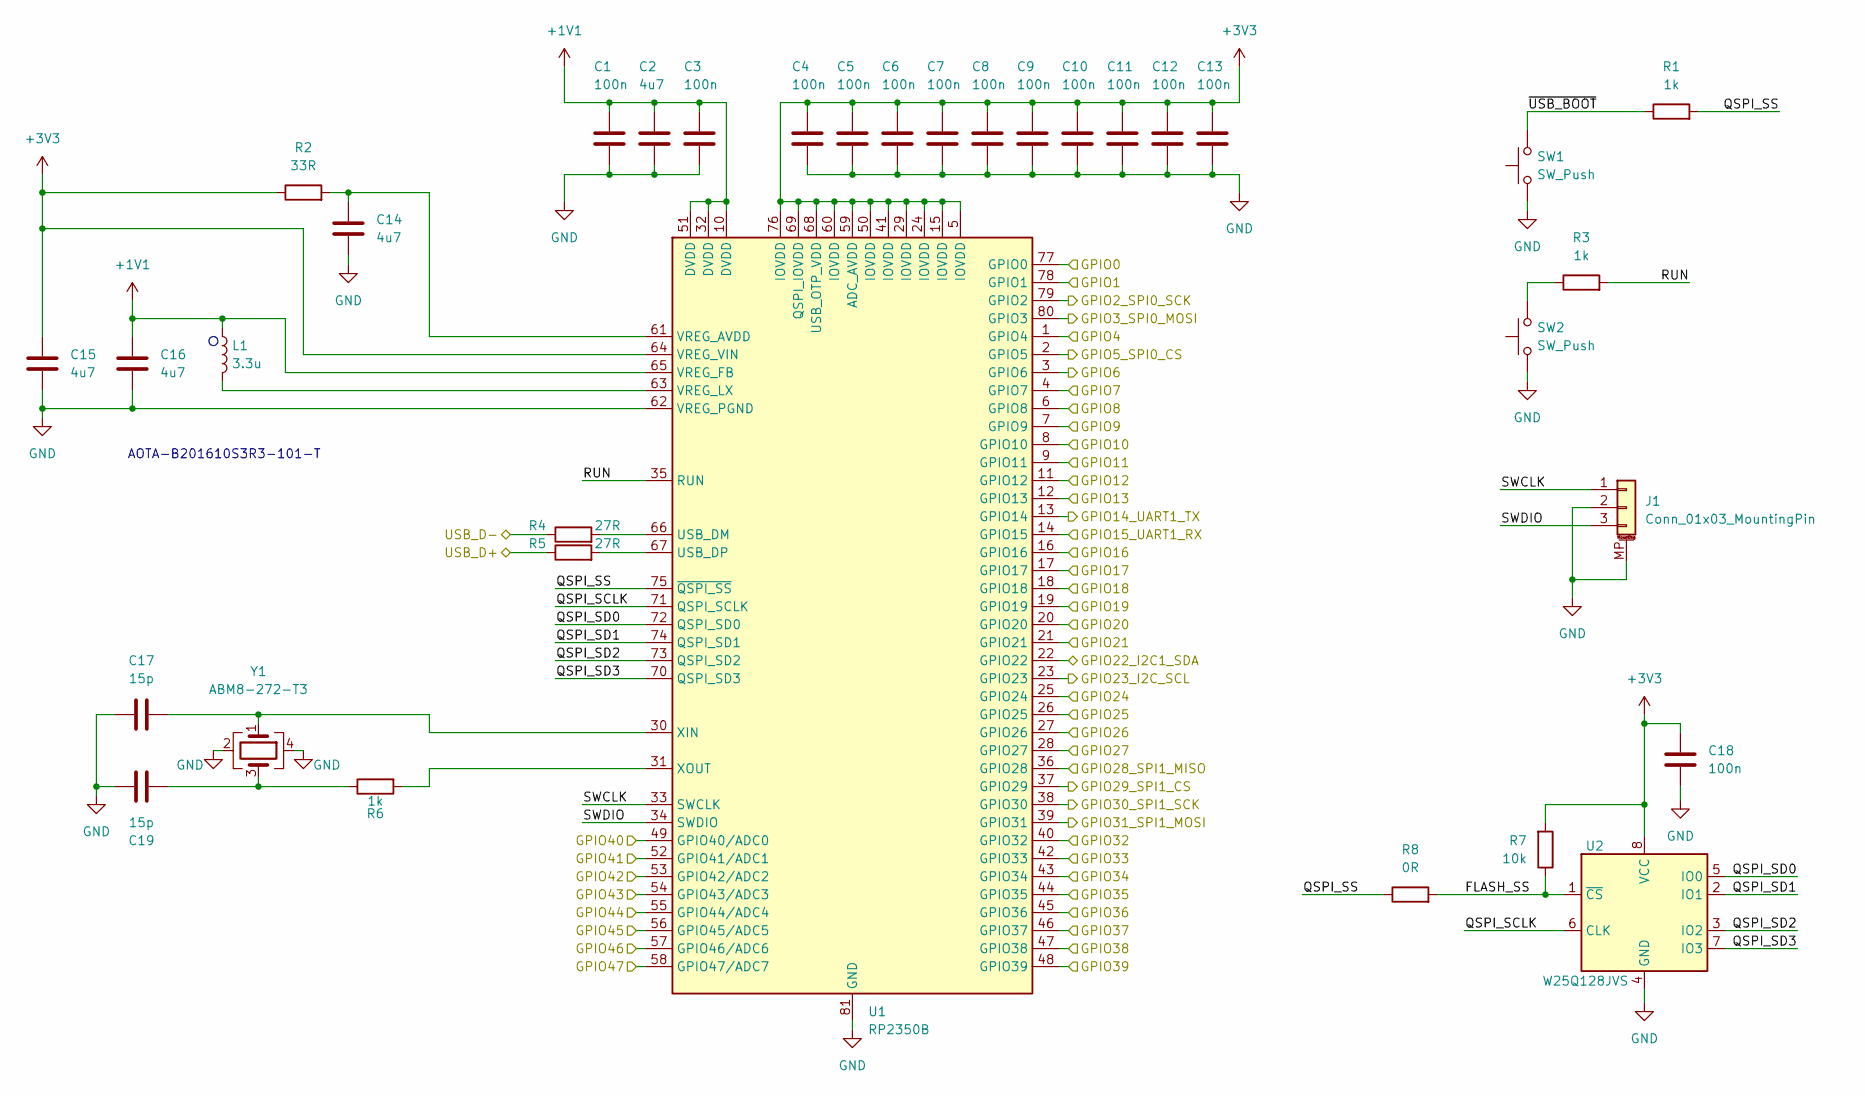
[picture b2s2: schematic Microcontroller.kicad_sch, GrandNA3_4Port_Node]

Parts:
C1, C3, C4, C5, C6, C7, C8, C9, C10, C11, C12, C13: 100n; C_0402_1005Metric
C2, C14, C15, C16: 4u7; C_0402_1005Metric
C17, C19: 15p; C_0402_1005Metric
C18: 100n; C_0603_1608Metric
J1: Conn_01x03_MountingPin; JST_SH_SM03B-SRSS-TB_1x03-1MP_P1.00mm_Horizontal
L1: 3.3u; IND-SMD_L2.0-W1.6_AOTA-B201610S3R3-101-T
R1, R3: 1k; R_0603_1608Metric
R2: 33R; R_0402_1005Metric
R4, R5: 27R; R_0402_1005Metric
R6: 1k; R_0402_1005Metric
R7: 10k; R_0603_1608Metric
R8: 0R; R_0603_1608Metric
SW1, SW2: SW_Push; SW_SPST_B3U-1000P
U1: RP2350B; QFN-80-1EP_10x10mm_P0.4mm_EP3.4x3.4mm
U2: W25Q128JVS; SOIC-8_5.3x5.3mm_P1.27mm
Y1: ABM8-272-T3; Crystal_SMD_3225-4Pin_3.2x2.5mm

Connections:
+1V1: C1.1, C2.1, C3.1, C16.1, L1.1, U1.10 (DVDD), U1.32 (DVDD), U1.51 (DVDD), U1.65 (VREG_FB)
+3V3: C4.1, C5.1, C6.1, C7.1, C8.1, C9.1, C10.1, C11.1, C12.1, C13.1, C15.1, C18.1, R2.1, R7.2, U1.5 (IOVDD), U1.15 (IOVDD), U1.24 (IOVDD), U1.29 (IOVDD), U1.41 (IOVDD), U1.50 (IOVDD), U1.59 (ADC_AVDD), U1.60 (IOVDD), U1.64 (VREG_VIN), U1.68 (USB_OTP_VDD), U1.69 (QSPI_IOVDD), U1.76 (IOVDD), U2.8 (VCC); also elsewhere on the board
/DMX/1_RDM_EN: U1.46 (GPIO37); also elsewhere on the board
/DMX/2_RDM_EN: U1.42 (GPIO33); also elsewhere on the board
/DMX/3_RDM_EN: U1.52 (GPIO41/ADC1); also elsewhere on the board
/DMX/4_RDM_EN: U1.56 (GPIO45/ADC5); also elsewhere on the board
/DMX/DMX_1_EN: U1.47 (GPIO38); also elsewhere on the board
/DMX/DMX_1_OUT: U1.48 (GPIO39); also elsewhere on the board
/DMX/DMX_1_RDM: U1.45 (GPIO36); also elsewhere on the board
/DMX/DMX_2_EN: U1.43 (GPIO34); also elsewhere on the board
/DMX/DMX_2_OUT: U1.44 (GPIO35); also elsewhere on the board
/DMX/DMX_2_RDM: U1.40 (GPIO32); also elsewhere on the board
/DMX/DMX_3_EN: U1.53 (GPIO42/ADC2); also elsewhere on the board
/DMX/DMX_3_OUT: U1.54 (GPIO43/ADC3); also elsewhere on the board
/DMX/DMX_3_RDM: U1.49 (GPIO40/ADC0); also elsewhere on the board
/DMX/DMX_4_EN: U1.57 (GPIO46/ADC6); also elsewhere on the board
/DMX/DMX_4_OUT: U1.58 (GPIO47/ADC7); also elsewhere on the board
/DMX/DMX_4_RDM: U1.55 (GPIO44/ADC4); also elsewhere on the board
/DMX/LEDs: U1.21 (GPIO21); also elsewhere on the board
/Display/BACKLIGHT: U1.77 (GPIO0); also elsewhere on the board
/Display/CS: U1.2 (GPIO5); also elsewhere on the board
/Display/ENC_A: U1.6 (GPIO8); also elsewhere on the board
/Display/ENC_B: U1.7 (GPIO9); also elsewhere on the board
/Display/ENC_SW: U1.4 (GPIO7); also elsewhere on the board
/Display/MOSI: U1.80 (GPIO3); also elsewhere on the board
/Display/RESET: U1.78 (GPIO1); also elsewhere on the board
/Display/RS: U1.3 (GPIO6); also elsewhere on the board
/Display/SCLK: U1.79 (GPIO2); also elsewhere on the board
/Ethernet/ACTLED: U1.27 (GPIO26); also elsewhere on the board
/Ethernet/INTERRUPT: U1.28 (GPIO27); also elsewhere on the board
/Ethernet/LINKLED: U1.26 (GPIO25); also elsewhere on the board
/Ethernet/MISO: U1.36 (GPIO28); also elsewhere on the board
/Ethernet/MOSI: U1.39 (GPIO31); also elsewhere on the board
/Ethernet/RST: U1.25 (GPIO24); also elsewhere on the board
/Ethernet/SCK: U1.38 (GPIO30); also elsewhere on the board
/Ethernet/SCS: U1.37 (GPIO29); also elsewhere on the board
/Microcontroller/FLASH_SS: R7.1, R8.2, U2.1 (~CS)
/Microcontroller/GPIO4: U1.1 (GPIO4)
/Microcontroller/GPIO10: U1.8 (GPIO10)
/Microcontroller/GPIO11: U1.9 (GPIO11); also elsewhere on the board
/Microcontroller/GPIO12: U1.11 (GPIO12); also elsewhere on the board
/Microcontroller/GPIO13: U1.12 (GPIO13); also elsewhere on the board
/Microcontroller/GPIO14_UART1_TX: U1.13 (GPIO14); also elsewhere on the board
/Microcontroller/GPIO15_UART1_RX: U1.14 (GPIO15); also elsewhere on the board
/Microcontroller/GPIO16: U1.16 (GPIO16); also elsewhere on the board
/Microcontroller/GPIO17: U1.17 (GPIO17); also elsewhere on the board
/Microcontroller/GPIO18: U1.18 (GPIO18); also elsewhere on the board
/Microcontroller/GPIO19: U1.19 (GPIO19); also elsewhere on the board
/Microcontroller/GPIO20: U1.20 (GPIO20); also elsewhere on the board
/Microcontroller/GPIO22_I2C1_SDA: U1.22 (GPIO22); also elsewhere on the board
/Microcontroller/GPIO23_I2C_SCL: U1.23 (GPIO23); also elsewhere on the board
/Microcontroller/QSPI_SCLK: U1.71 (QSPI_SCLK), U2.6 (CLK)
/Microcontroller/QSPI_SD0: U1.72 (QSPI_SD0), U2.5 (IO0)
/Microcontroller/QSPI_SD1: U1.74 (QSPI_SD1), U2.2 (IO1)
/Microcontroller/QSPI_SD2: U1.73 (QSPI_SD2), U2.3 (IO2)
/Microcontroller/QSPI_SD3: U1.70 (QSPI_SD3), U2.7 (IO3)
/Microcontroller/QSPI_SS: R1.2, R8.1, U1.75 (~QSPI_SS)
/Microcontroller/RUN: R3.2, U1.35 (RUN)
/Microcontroller/SWCLK: J1.1, U1.33 (SWCLK)
/Microcontroller/SWDIO: J1.3, U1.34 (SWDIO)
/Microcontroller/~USB_BOOT: R1.1, SW1.2
/USB/USB_D+: R5.1; also elsewhere on the board
/USB/USB_D-: R4.1; also elsewhere on the board
GND: C1.2, C2.2, C3.2, C4.2, C5.2, C6.2, C7.2, C8.2, C9.2, C10.2, C11.2, C12.2, C13.2, C14.2, C15.2, C16.2, C17.1, C18.2, C19.1, J1.2, J1.MP (MountPin), SW1.1, SW2.1, U1.62 (VREG_PGND), U1.81 (GND), U2.4 (GND), Y1.2 (G), Y1.4 (G); also elsewhere on the board
unnamed: C19.2, R6.1, Y1.3
unnamed: R3.1, SW2.2
unnamed: R4.2, U1.66 (USB_DM)
unnamed: R5.2, U1.67 (USB_DP)
unnamed: C14.1, R2.2, U1.61 (VREG_AVDD)
unnamed: L1.2, U1.63 (VREG_LX)
unnamed: C17.2, U1.30 (XIN), Y1.1
unnamed: R6.2, U1.31 (XOUT)

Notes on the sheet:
AOTA-B201610S3R3-101-T

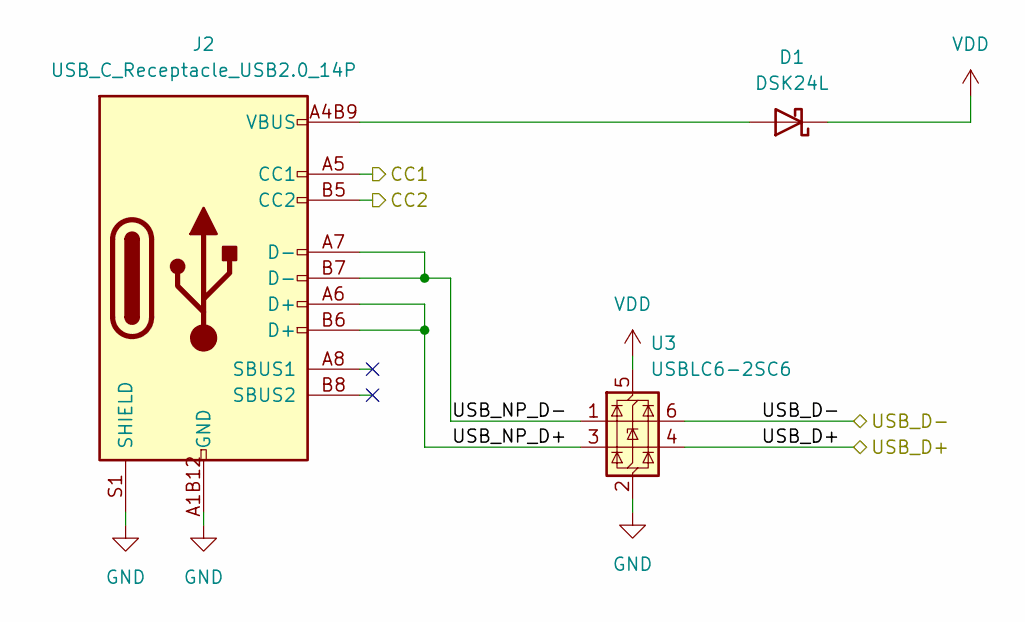
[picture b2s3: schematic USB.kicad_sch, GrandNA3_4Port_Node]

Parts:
D1: DSK24L; D_SOD-123F
J2: USB_C_Receptacle_USB2.0_14P; USB-C_SMD-TYPE-C-31-M-12_1
U3: USBLC6-2SC6; SOT-23-6

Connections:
/POWER/CC1: J2.A5 (CC1); also elsewhere on the board
/POWER/CC2: J2.B5 (CC2); also elsewhere on the board
/USB/USB_D+: U3.4 (I/O2); also elsewhere on the board
/USB/USB_D-: U3.6 (I/O1); also elsewhere on the board
/USB/USB_NP_D+: J2.A6 (D+), J2.B6 (D+), U3.3 (I/O2)
/USB/USB_NP_D-: J2.A7 (D-), J2.B7 (D-), U3.1 (I/O1)
GND: J2.A1B12 (GND), J2.B1A12 (GND), J2.S1 (SHIELD), U3.2 (GND); also elsewhere on the board
unnamed: D1.2 (A), J2.A4B9 (VBUS), J2.B4A9 (VBUS)
VDD: D1.1 (K), U3.5 (VBUS); also elsewhere on the board
